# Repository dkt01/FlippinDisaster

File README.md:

# FlippinDisaster
Flipper type battlebot

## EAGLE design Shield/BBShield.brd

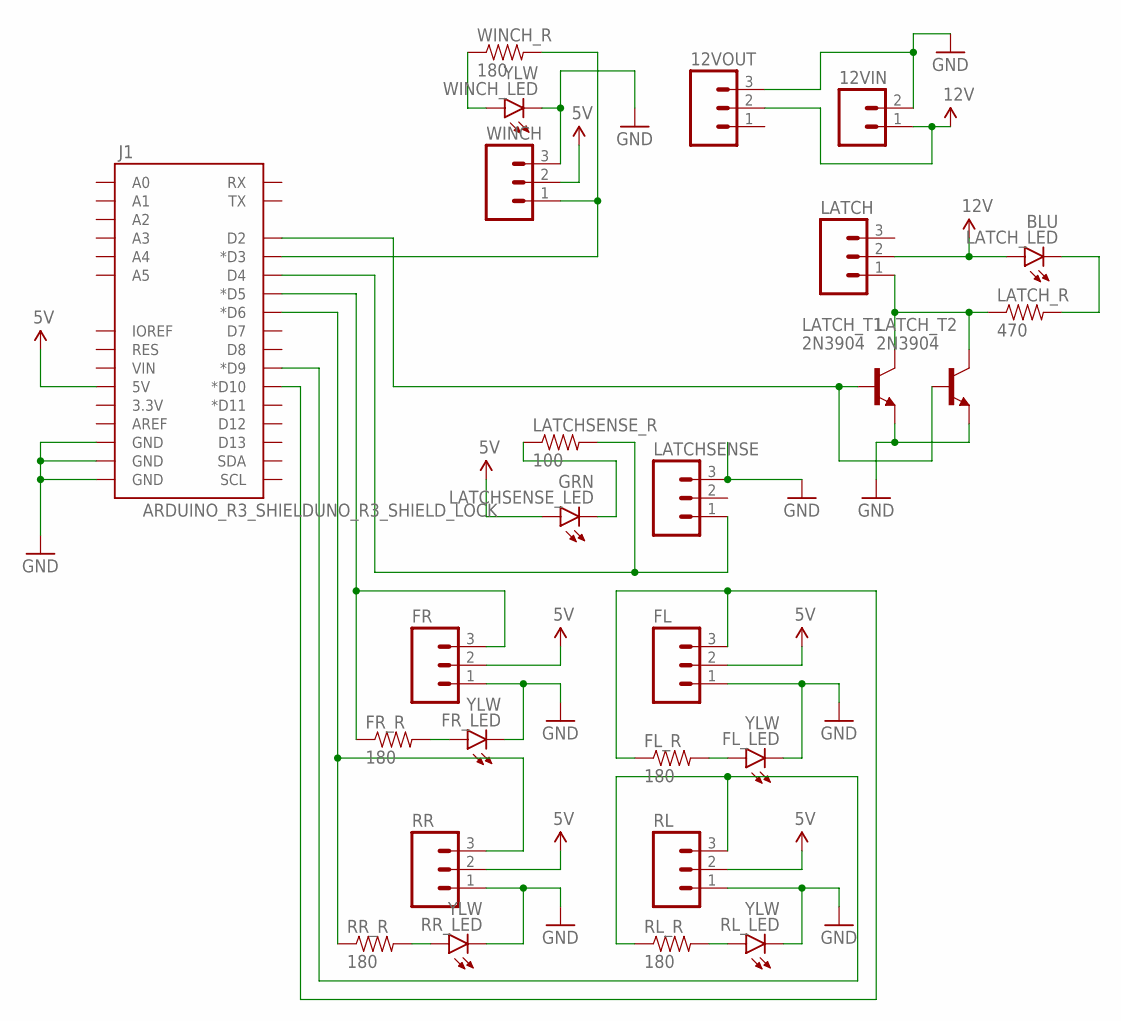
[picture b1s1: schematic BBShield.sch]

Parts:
12VIN: M025MM; SCREWTERMINAL-5MM-2
12VOUT: M03LOCK; 1X03_LOCK
FL: M03LOCK; 1X03_LOCK
FL_LED: YLW; LED3MM
FL_R: 180; AXIAL-0.4
FR: M03LOCK; 1X03_LOCK
FR_LED: YLW; LED3MM
FR_R: 180; AXIAL-0.4
J1: ARDUINO_R3_SHIELDUNO_R3_SHIELD_LOCK; UNO_R3_SHIELD_LOCK
LATCH: M03LOCK; 1X03_LOCK
LATCHSENSE: M03LOCK; 1X03_LOCK
LATCHSENSE_LED: GRN; LED3MM
LATCHSENSE_R: 100; AXIAL-0.4
LATCH_LED: BLU; LED3MM
LATCH_R: 470; AXIAL-0.4
LATCH_T1, LATCH_T2: 2N3904; TO92
RL: M03LOCK; 1X03_LOCK
RL_LED: YLW; LED3MM
RL_R: 180; AXIAL-0.4
RR: M03LOCK; 1X03_LOCK
RR_LED: YLW; LED3MM
RR_R: 180; AXIAL-0.4
WINCH: M03LOCK; 1X03_LOCK
WINCH_LED: YLW; LED3MM
WINCH_R: 180; AXIAL-0.4

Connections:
5V: FL.2, FR.2, J1.5V, LATCHSENSE_LED.A, RL.2, RR.2, WINCH.2
12V: 12VIN.1, 12VOUT.2, LATCH.2, LATCH_LED.A
D2: J1.D2, LATCH_T1.2 (B), LATCH_T2.2 (B)
D3: J1.D3 (*D3), WINCH.1, WINCH_R.P$2 (2)
D4: J1.D4, LATCHSENSE.1, LATCHSENSE_R.P$2 (2)
D5: FR.3, FR_R.P$1 (1), J1.D5 (*D5)
D6: J1.D6 (*D6), RR.3, RR_R.P$1 (1)
D9: J1.D9 (*D9), RL.3, RL_R.P$1 (1)
D10: FL.3, FL_R.P$1 (1), J1.D10 (*D10)
GND: 12VIN.2, 12VOUT.3, FL.1, FL_LED.K (C), FR.1, FR_LED.K (C), J1.GND@0 (GND), J1.GND@1 (GND), J1.GND@2 (GND), LATCHSENSE.3, LATCH_T1.3 (E), LATCH_T2.3 (E), RL.1, RL_LED.K (C), RR.1, RR_LED.K (C), WINCH.3, WINCH_LED.K (C)
unnamed: LATCHSENSE_LED.K (C), LATCHSENSE_R.P$1 (1)
unnamed: FR_LED.A, FR_R.P$2 (2)
unnamed: WINCH_LED.A, WINCH_R.P$1 (1)
unnamed: LATCH.1, LATCH_R.P$1 (1), LATCH_T1.1 (C), LATCH_T2.1 (C)
unnamed: RR_LED.A, RR_R.P$2 (2)
unnamed: RL_LED.A, RL_R.P$2 (2)
unnamed: FL_LED.A, FL_R.P$2 (2)
unnamed: LATCH_LED.K (C), LATCH_R.P$2 (2)

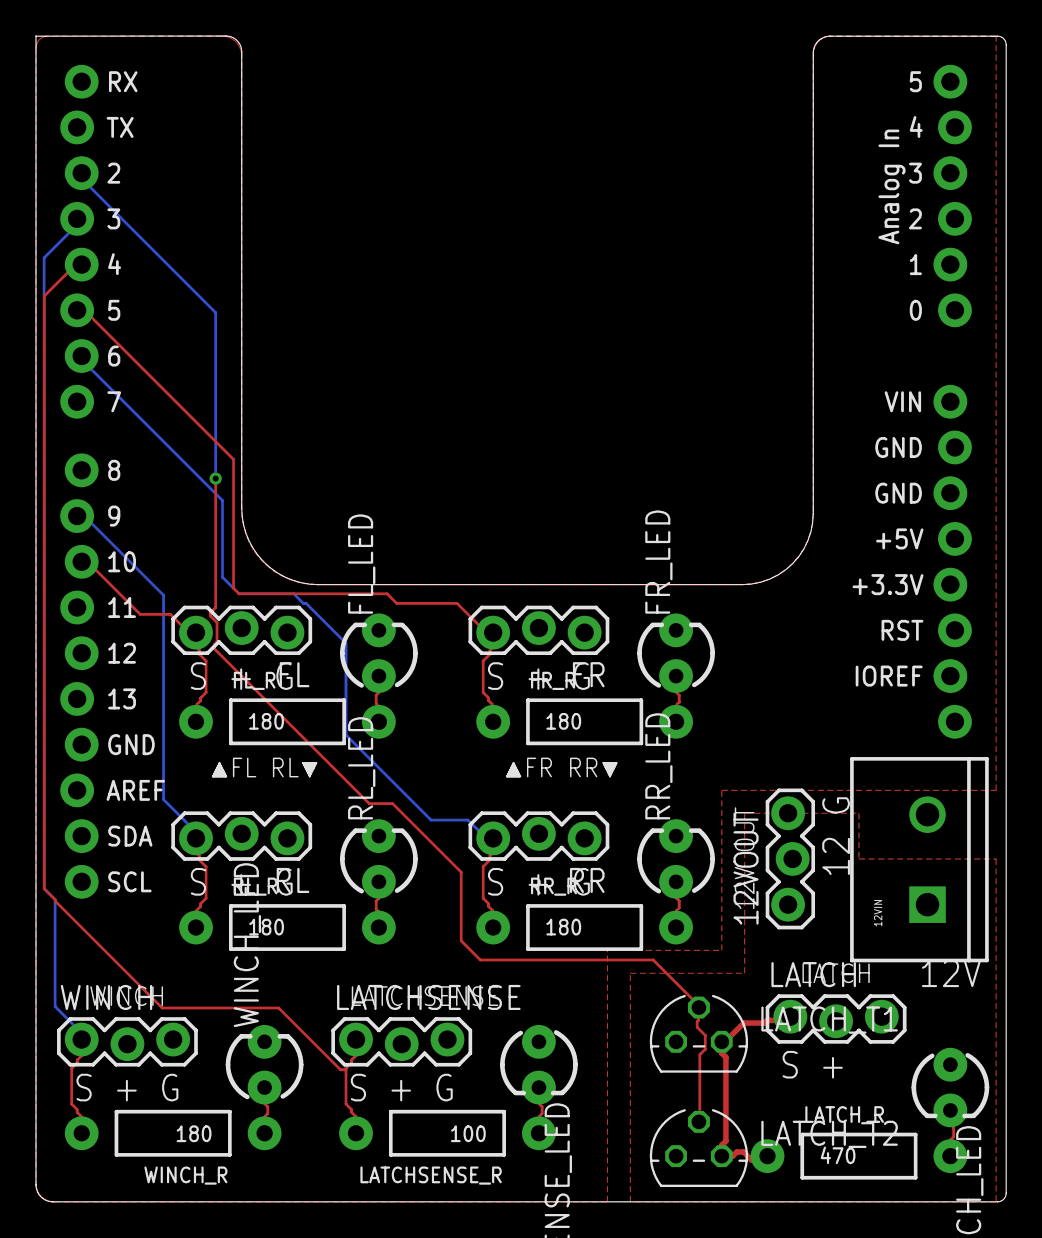
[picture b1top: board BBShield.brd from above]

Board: 2 copper layers, 53.9 x 64.8 mm, 26 parts (0 on the bottom side), 18 nets.

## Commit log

2017-04-09 Added files to Git

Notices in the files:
parts and their libraries:
SparkFun-Connectors: Licensing: Creative Commons ShareAlike 4.0 International - https://creativecommons.org/licenses/by-sa/4.0
